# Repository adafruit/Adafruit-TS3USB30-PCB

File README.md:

## Adafruit TS3USB30 1 to 2 USB Switch PCB

<a href="http://www.adafruit.com/products/5871"><br/>
Click here to purchase one from the Adafruit shop</a>

PCB files for the Adafruit TS3USB30 1 to 2 USB Switch. 

Format is EagleCAD schematic and board layout
* https://www.adafruit.com/product/5871

### Description

The Adafruit TS3USB30 1 to 2 USB Switch is a nifty breakout board for the TI TS3USB30 that will let you connect one of two USB devices to a single port, handy when you have multiple chips that you may want to communicate over USB but you don't want a hub. This breakout will connect one or the other - it's designed specifically for USB so it can handle high bandwidth USB 2.0 connections of 480 Mbps.

Usage is quite simple: there is one 'upstream' connection, use that to connect to the USB Host device like a computer or Host-capable microprocessor. You can use either the USB Type C port or the breakout pads at the bottom. Then connect two different USB peripherals to the power/ground/D+/D- lines on either side. The S pin selects which port is active, low signal is port 1, high signal is port 2. The Output Enable pin lets you disconnect both. 

Note that power is not switched, just data! Both sides will be powered as the switch connects from one to the other. So, you need your peripherals to know when USB data has been disconnected if you want them to act differently or to re-enumerate. We noticed that solid-state chips like FT232's and USB sticks were great about this, but microcontrollers could be confused and not re-enumerate because they only enumerate on power up. In that case, you'll want to also reset the device via it's own Reset or Enable pin.

The breakout board comes fully assembled, with a 3.3V regulator from 5V and a green power LED that can be disabled. Some header is also included if you'd like to use it in a breadboard - you may find you're maxed out at 12 Mbps speeds though. Four mounting holes make it easy to attach anywhere you like. 

### License

Adafruit invests time and resources providing this open source design, please support Adafruit and open-source hardware by purchasing products from [Adafruit](https://www.adafruit.com)!

Designed by Limor Fried/Ladyada for Adafruit Industries.

Creative Commons Attribution/Share-Alike, all text above must be included in any redistribution. 
See license.txt for additional details.

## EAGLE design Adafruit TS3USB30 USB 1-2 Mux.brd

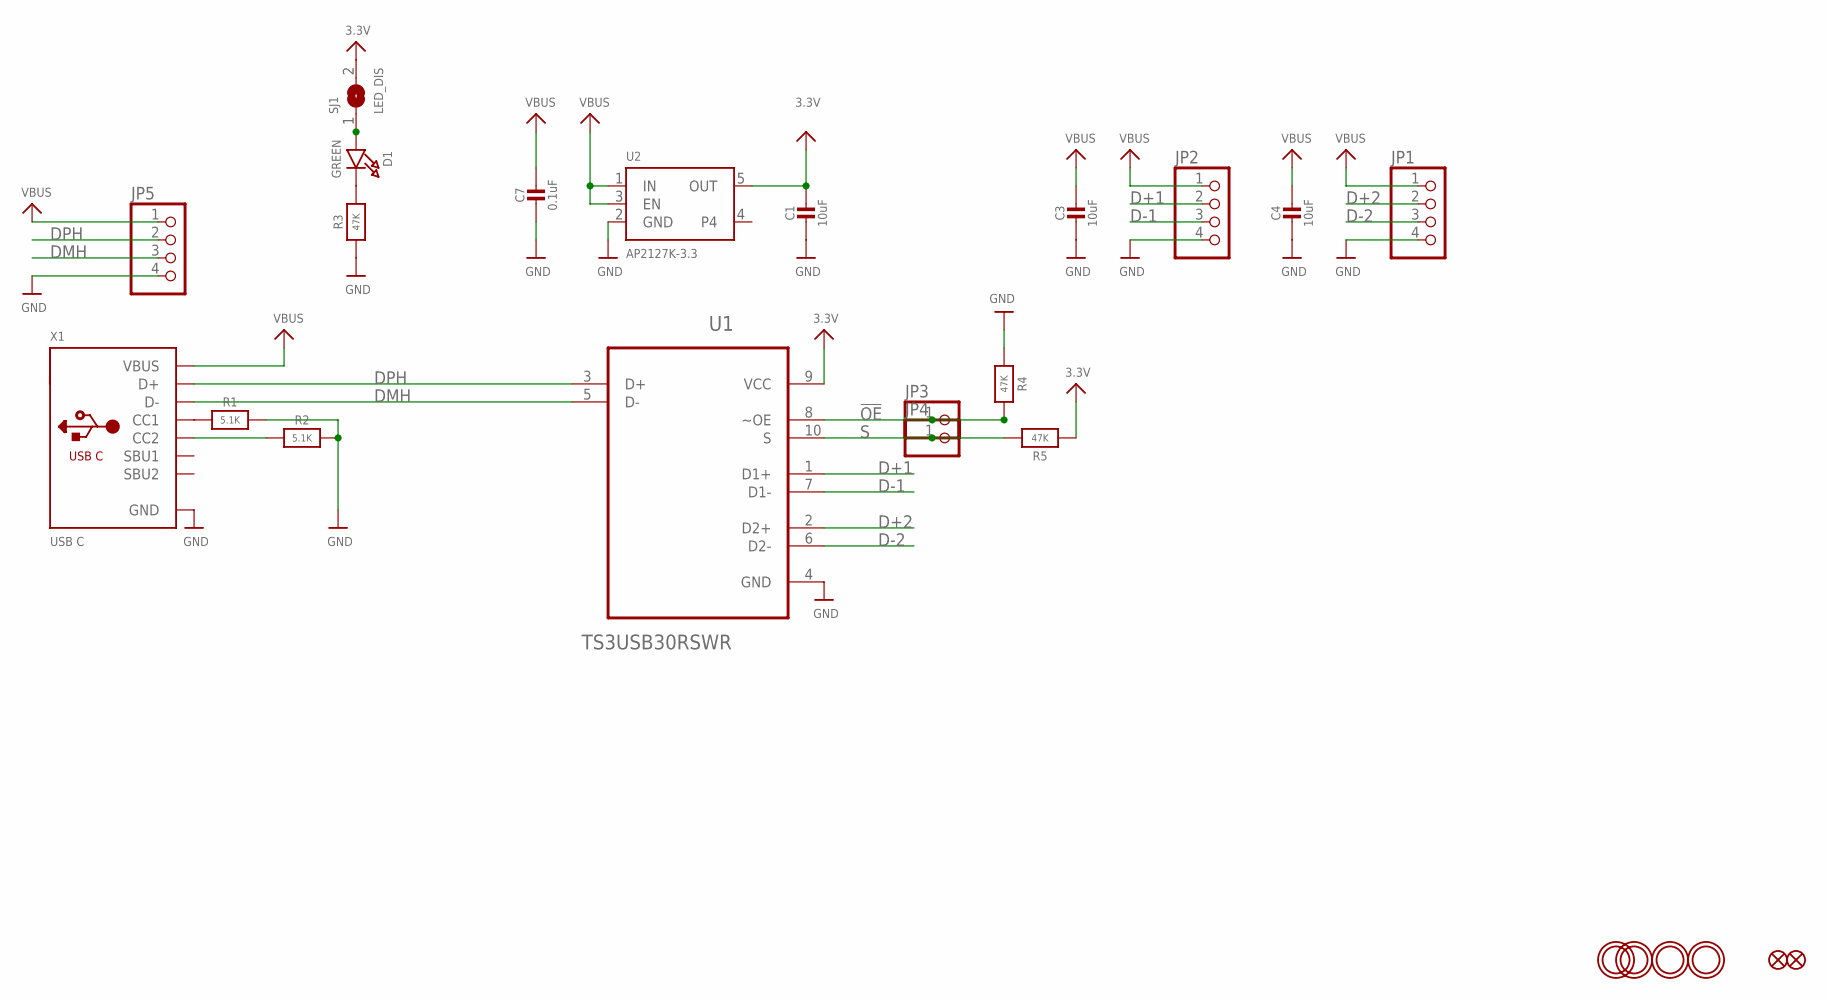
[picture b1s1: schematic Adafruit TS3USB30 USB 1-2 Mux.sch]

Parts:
C1, C3, C4: 10uF; 0805-NO
C7: 0.1uF; 0603-NO
D1: GREEN; CHIPLED_0603_NOOUTLINE
FID1, FID2: FIDUCIAL_1MM
JP1, JP2, JP5: HEADER-1X4ROUND; 1X04_ROUND
JP3, JP4: HEADER-1X1ROUND_76MIL; 1X01_ROUND_76MIL
R1, R2: 5.1K; 0603-NO
R3, R4, R5: 47K; 0603-NO
SJ1: LED_DIS; SOLDERJUMPER_CLOSEDWIRE
U1: TS3USB30RSWR; 10-UFQFN
U2: AP2127K-3.3; SOT23-5
U$23, U$28, U$29, U$31: MOUNTINGHOLE2.5; MOUNTINGHOLE_2.5_PLATED
X1: USB C; USB_C_CUSB31-CFM2AX-01-X

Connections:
3.3V: C1.1, R5.1, SJ1.2, U1.9 (VCC), U2.5 (OUT)
!OE: JP3.1, R4.2, U1.8 (~OE)
D+1: JP2.2, U1.1 (D1+)
D+2: JP1.2, U1.2 (D2+)
D-1: JP2.3, U1.7 (D1-)
D-2: JP1.3, U1.6 (D2-)
DMH: JP5.3, U1.5 (D-), X1.A7 (D-), X1.B7 (D-)
DPH: JP5.2, U1.3 (D+), X1.A6 (D+), X1.B6 (D+)
GND: C1.2, C3.2, C4.2, C7.2, JP1.4, JP2.4, JP5.4, R1.2, R2.2, R3.1, R4.1, U1.4 (GND), U2.2 (GND), X1.A1B12 (GND), X1.B1A12 (GND)
unnamed: R1.1, X1.A5 (CC1)
unnamed: R2.1, X1.B5 (CC2)
unnamed: D1.A, SJ1.1
unnamed: D1.C, R3.2
S: JP4.1, R5.2, U1.10 (S)
VBUS: C3.1, C4.1, C7.1, JP1.1, JP2.1, JP5.1, U2.1 (IN), U2.3 (EN), X1.A4B9 (VBUS), X1.B4A9 (VBUS)

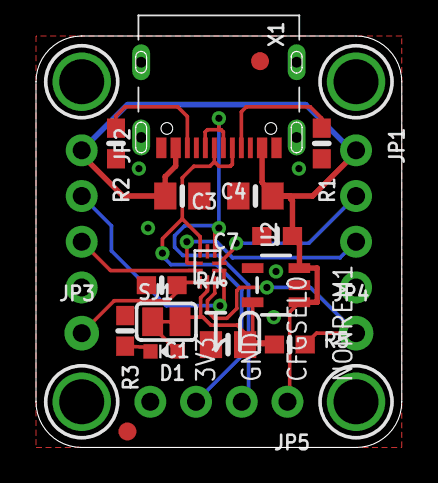
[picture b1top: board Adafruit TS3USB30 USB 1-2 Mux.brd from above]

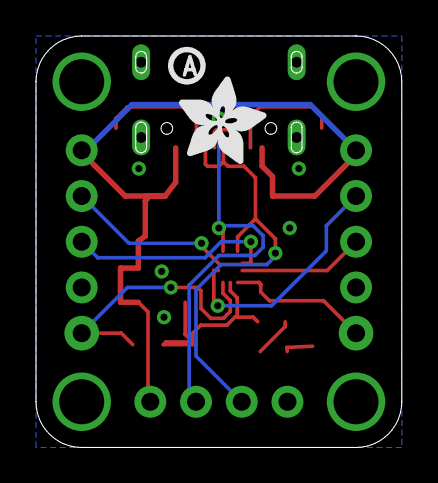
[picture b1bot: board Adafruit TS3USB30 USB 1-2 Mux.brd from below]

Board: 2 copper layers, 20.3 x 22.9 mm, 45 parts (3 on the bottom side), 15 nets.

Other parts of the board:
PLABEL0: PLABEL0
PLABEL1: PLABEL1
PLABEL2: PLABEL2
PLABEL3: PLABEL3
PLABEL4: PLABEL4
PLABEL5: PLABEL5
PLABEL6: PLABEL6
PLABEL7: PLABEL7
PLABEL8: PLABEL8
PLABEL9: PLABEL9
PLABEL10: PLABEL10
PLABEL11: PLABEL11
PLABEL12: PLABEL12
PLABEL13: PLABEL13
PLABEL14: PLABEL14
PLABEL15: PLABEL15
PLABEL16: PLABEL16
PLABEL17: PLABEL17
U$33: ADAFRUIT_5MM
U$34: PCBFEAT-REV-040

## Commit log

2024-01-09 cookiecutter
2024-01-09 rename

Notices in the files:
parts and their libraries:
microbuilder: This work is placed in the public domain, and may be freely used for commercial and non-commercial work with the following conditions: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
